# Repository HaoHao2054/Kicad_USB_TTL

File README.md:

# 说明

使用kicad绘制pcb，并用git和GitHub进行管理。这个是我使用这种工作流程的测试项目

## 一、原理图预览

## 二、PCB预览

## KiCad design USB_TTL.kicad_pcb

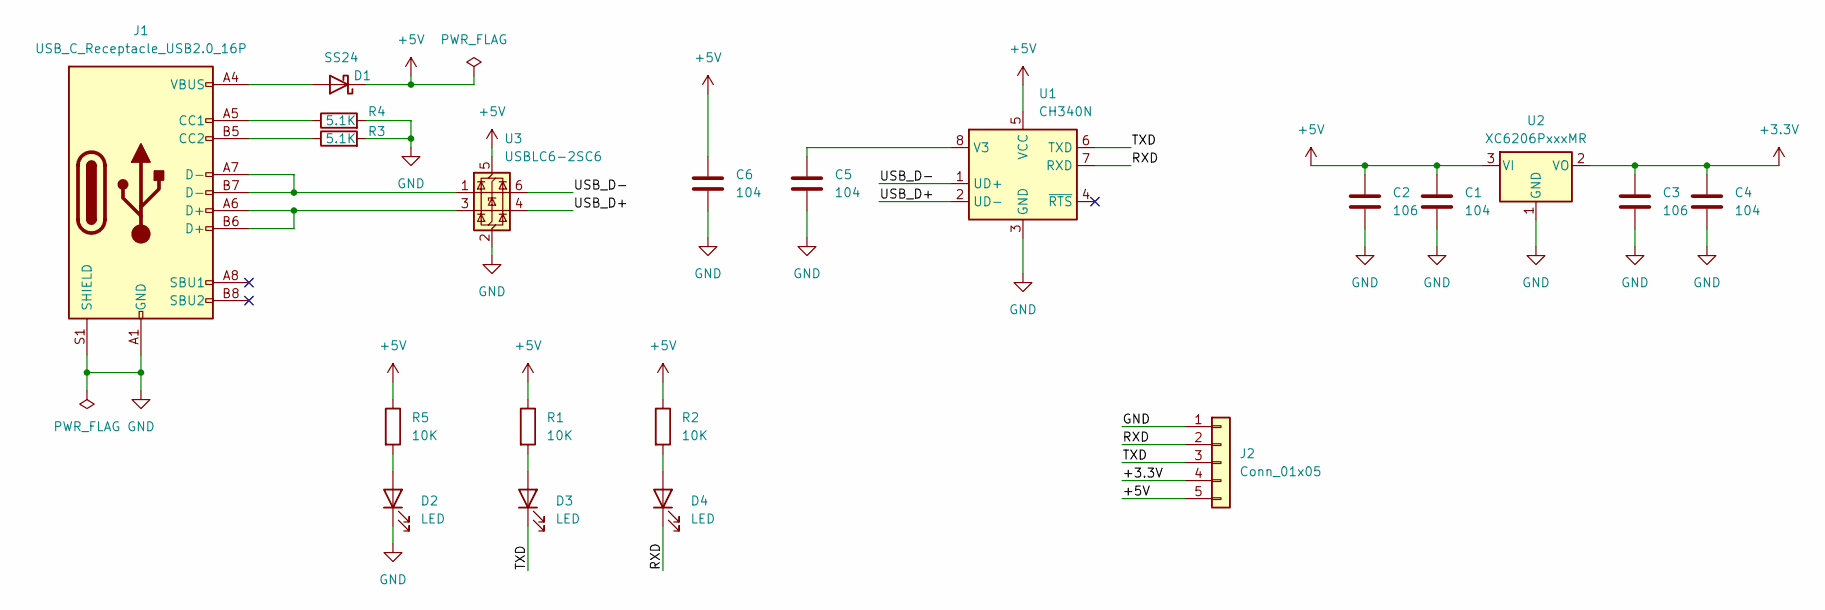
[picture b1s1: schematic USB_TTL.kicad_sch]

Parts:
C1, C4, C5, C6: 104; C_0603_1608Metric
C2, C3: 106; C_0603_1608Metric
D1: SS24; D_SMA
D2, D3, D4: LED; LED_0603_1608Metric
J1: USB_C_Receptacle_USB2.0_16P; USB_C_Receptacle_Palconn_UTC16-G
J2: Conn_01x05; PinHeader_1x05_P2.54mm_Vertical
R1, R2, R5: 10K; R_0603_1608Metric
R3, R4: 5.1K; R_0603_1608Metric
U1: CH340N; SOP-8_3.9x4.9mm_P1.27mm
U2: XC6206PxxxMR; SOT-23-3
U3: USBLC6-2SC6; SOT-23-6

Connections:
+3.3V: C3.1, C4.1, J2.4, U2.2 (VO)
+5V: C1.1, C2.1, C6.1, D1.1 (K), J2.5, R1.1, R2.1, R5.1, U1.5 (VCC), U2.3 (VI), U3.5 (VBUS)
/RXD: D4.1 (K), J2.2, U1.7 (RXD)
/TXD: D3.1 (K), J2.3, U1.6 (TXD)
/USB_D+: U1.2 (UD-), U3.4 (I/O2)
/USB_D-: U1.1 (UD+), U3.6 (I/O1)
GND: C1.2, C2.2, C3.2, C4.2, C5.2, C6.2, D2.1 (K), J1.A1 (GND), J1.A12 (GND), J1.B1 (GND), J1.B12 (GND), J1.S1 (SHIELD), J2.1, R3.2, R4.2, U1.3 (GND), U2.1 (GND), U3.2 (GND)
unnamed: D1.2 (A), J1.A4 (VBUS), J1.A9 (VBUS), J1.B4 (VBUS), J1.B9 (VBUS)
unnamed: D2.2 (A), R5.2
unnamed: D3.2 (A), R1.2
unnamed: D4.2 (A), R2.2
unnamed: J1.A5 (CC1), R4.1
unnamed: J1.B5 (CC2), R3.1
unnamed: J1.A6 (D+), J1.B6 (D+), U3.3 (I/O2)
unnamed: J1.A7 (D-), J1.B7 (D-), U3.1 (I/O1)
unnamed: C5.1, U1.8 (V3)

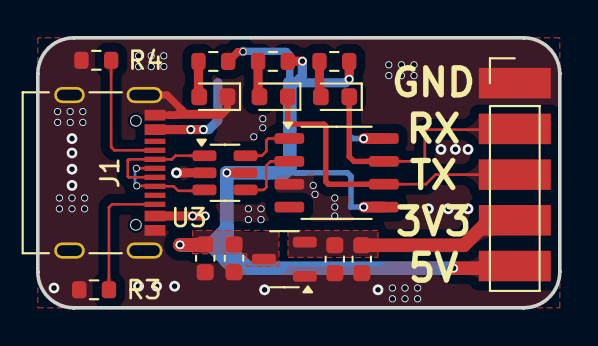
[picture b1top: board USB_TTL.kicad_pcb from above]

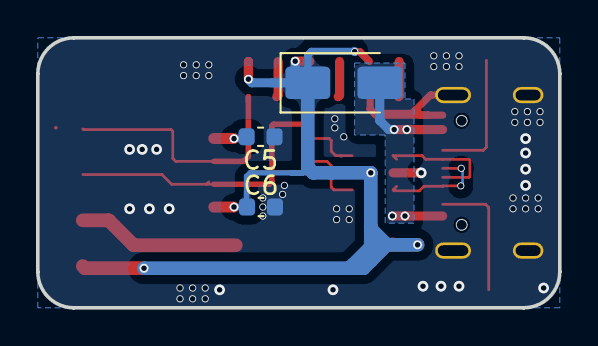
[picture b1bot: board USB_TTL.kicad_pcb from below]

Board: 2 copper layers, 29.0 x 15.0 mm, 20 parts (3 on the bottom side), 16 nets.

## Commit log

2025-05-27 initial
2025-05-27 添加readme
